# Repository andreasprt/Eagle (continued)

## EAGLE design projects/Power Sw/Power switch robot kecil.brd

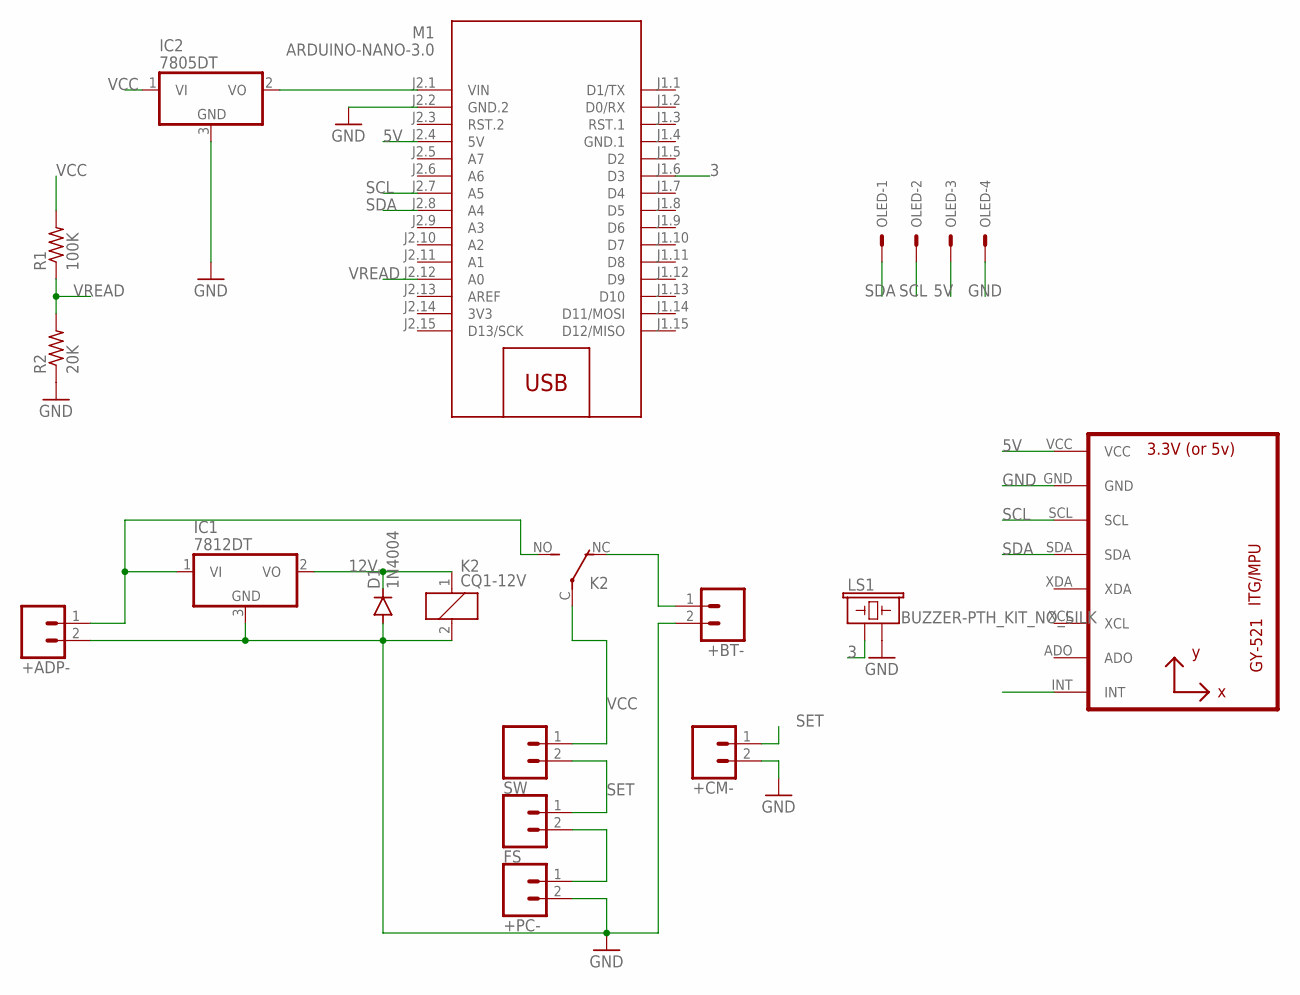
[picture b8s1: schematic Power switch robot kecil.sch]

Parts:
+ADP-: CONN_02PTH4; 1X02_XTRA_BIG
+BT-: CONN_02PTH4; 1X02_XTRA_BIG
+CM-: CONN_02PTH4; 1X02_XTRA_BIG
+PC-: CONN_02PTH4; 1X02_XTRA_BIG
D1: 1N4004; DO41-10
FS: CONN_02PTH4; 1X02_XTRA_BIG
IC1: 7812DT; TO252
IC2: 7805DT; TO252
K2: CQ1-12V; CQ1
LS1: BUZZER-PTH_KIT_NO_SILK; BUZZER-12MM-NS-KIT
M1: ARDUINO-NANO-3.0
OLED: 22-27-2041-04; 6410-04
R1: 100K; 0207/10
R2: 20K; 0207/10
SW: CONN_02PTH4; 1X02_XTRA_BIG
U1: GY-521MPU6050; GY-521

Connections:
3: LS1.+ (1), M1.J1.6 (D3)
3V3: M1.J2.14 (3V3)
5V: M1.J2.4 (5V), OLED.3, U1.VCC
12V: D1.C, IC1.2 (VO), K2.1
GND: +ADP-.2, +BT-.2, +CM-.2, +PC-.2, D1.A, IC1.3 (GND), IC2.3 (GND), K2.2, LS1.- (2), M1.J2.2 (GND.2), OLED.4, R2.1, U1.GND
GND.1: M1.J1.4 (GND.1)
unnamed: +ADP-.1, IC1.1 (VI), K2.NO (S)
unnamed: +BT-.1, K2.NC (O)
unnamed: +PC-.1, FS.2
unnamed: IC2.2 (VO), M1.J2.1 (VIN)
SCL: M1.J2.7 (A5), OLED.2, U1.SCL
SDA: M1.J2.8 (A4), OLED.1, U1.SDA
SET: +CM-.1, FS.1, SW.2
VCC: IC2.1 (VI), K2.C, R1.2, SW.1
VREAD: M1.J2.12 (A0), R1.1, R2.2

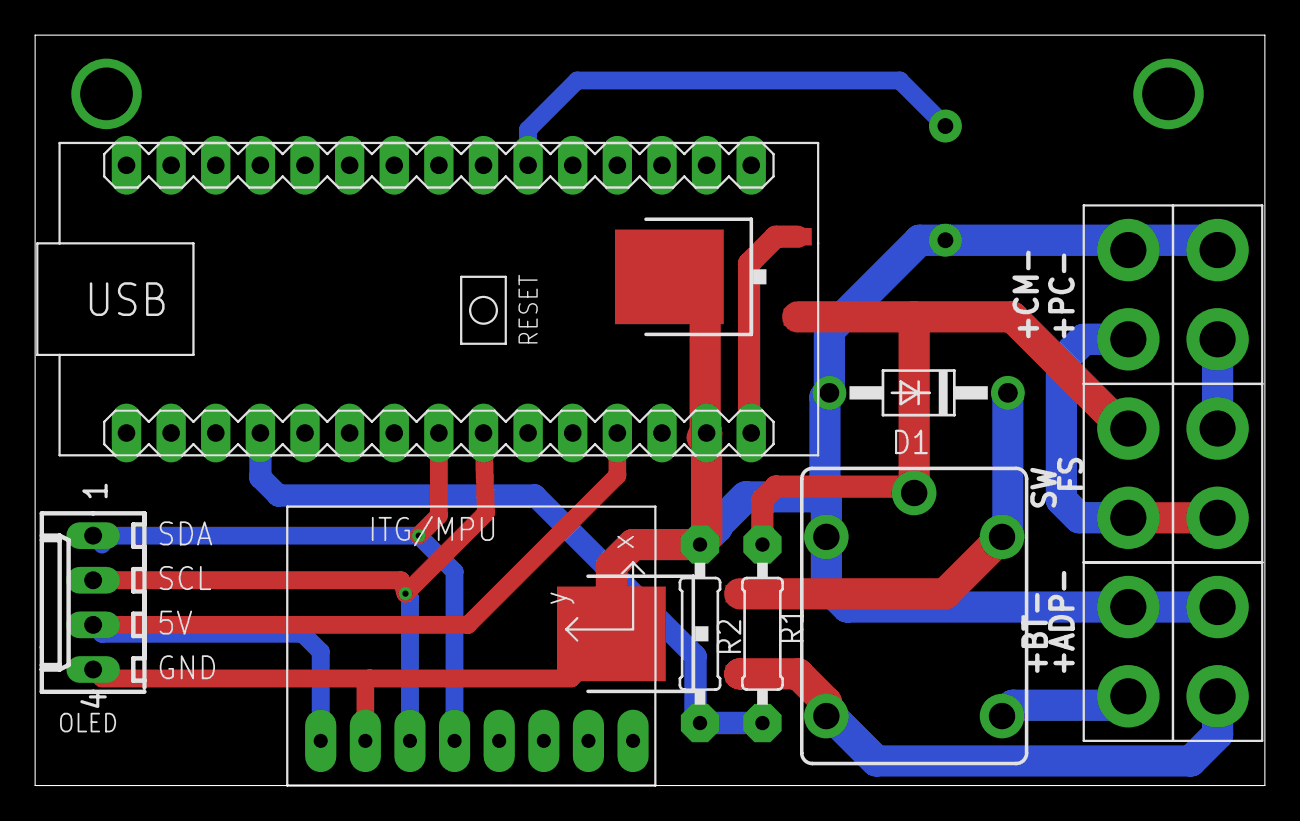
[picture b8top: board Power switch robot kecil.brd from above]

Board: 2 copper layers, 70.0 x 42.7 mm, 16 parts (0 on the bottom side), 13 nets.

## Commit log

2021-08-29 membuat repo
2021-08-29 menambah library
